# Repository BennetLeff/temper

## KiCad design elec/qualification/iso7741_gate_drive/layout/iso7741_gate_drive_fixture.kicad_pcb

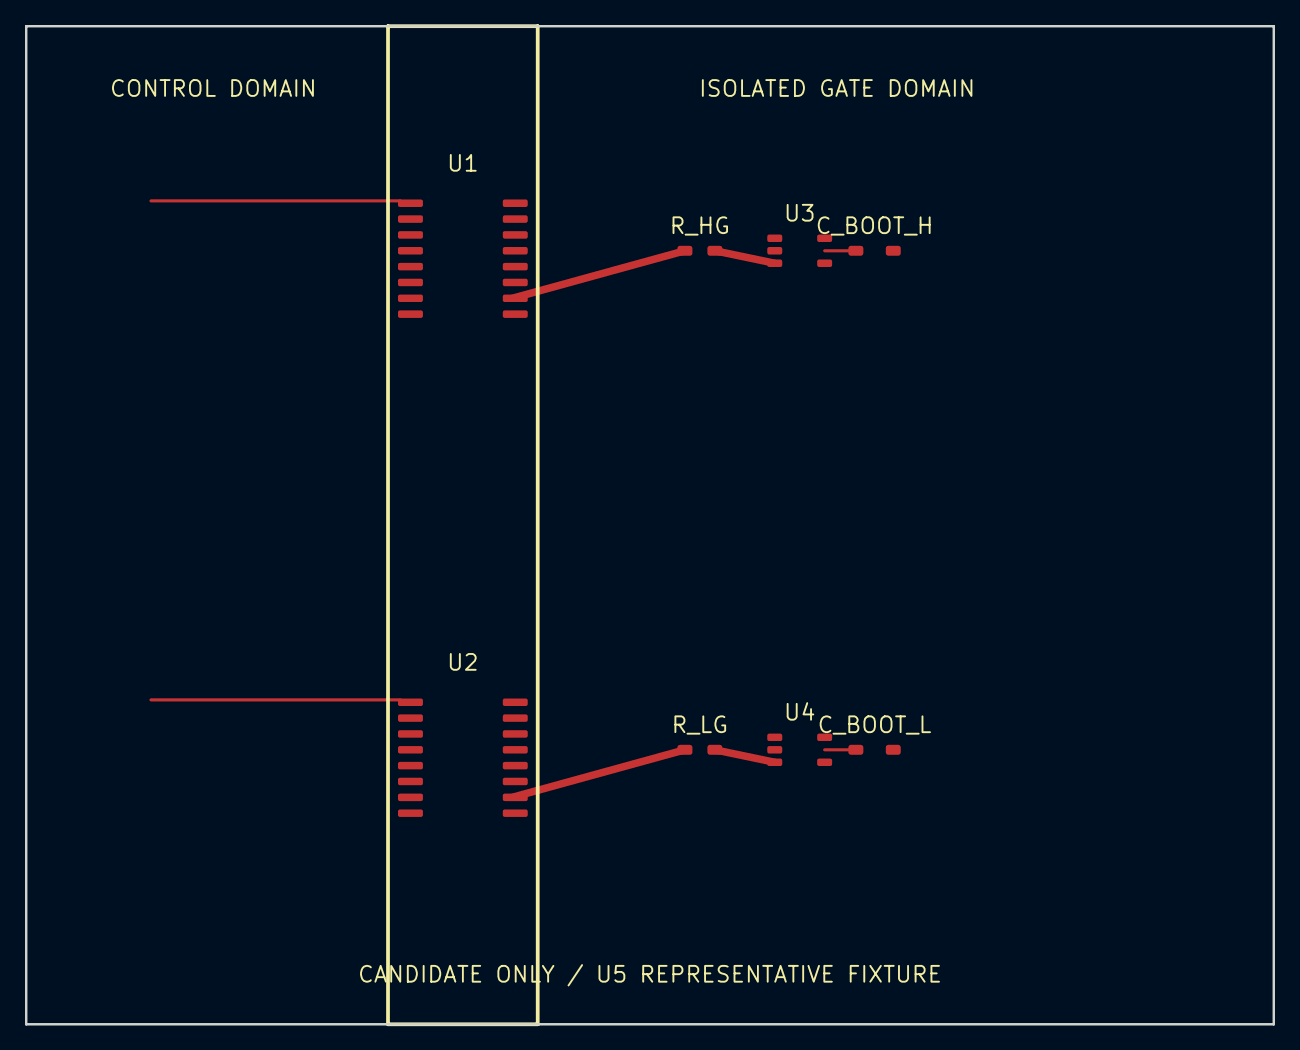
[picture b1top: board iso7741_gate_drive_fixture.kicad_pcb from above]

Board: 2 copper layers, 100.0 x 80.0 mm, 8 parts (0 on the bottom side), 12 nets.

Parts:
C_BOOT_H: 100nF; Bootstrap_HS
C_BOOT_L: 100nF; Bootstrap_LS
R_HG: 4R7_GATE; R_0603_1608Metric
R_LG: 4R7_GATE; R_0603_1608Metric
U1, U2: ISO7741FQDWWRQ1; ISO7741_DWW16
U3, U4: UCC27517AQDBVRQ1; Package_DBV5

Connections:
+15V_HS: C_BOOT_H.2, U3.5
+15V_LS: C_BOOT_L.2, U4.5
CTRL_GND: U1.3 (GND1), U1.5 (GND1), U1.7 (GND1), U2.3 (GND1), U2.5 (GND1), U2.7 (GND1)
GATE_HS: R_HG.1, R_HG.2, U1.10 (Y1), U1.11 (Y2), U3.3
GATE_HS_RETURN: U1.9 (GND2), U1.12 (GND2), U3.2
GATE_LS: R_LG.1, R_LG.2, U2.10 (Y1), U2.11 (Y2), U4.3
GATE_LS_RETURN: U2.9 (GND2), U2.12 (GND2), U4.2
GATE_SAFE_HS: U1.6 (EN1), U3.4
GATE_SAFE_LS: U2.6 (EN1), U4.4
ISO_HS_VDD: U1.4 (VCC1), U1.8 (VCC1)
ISO_LS_OUT: U1.15 (Y3), U3.1, U4.1
ISO_LS_VDD: U1.13 (VCC2), U1.14 (VCC2), U1.16 (VCC2), U2.4 (VCC1), U2.8 (VCC1), U2.13 (VCC2), U2.14 (VCC2), U2.16 (VCC2)

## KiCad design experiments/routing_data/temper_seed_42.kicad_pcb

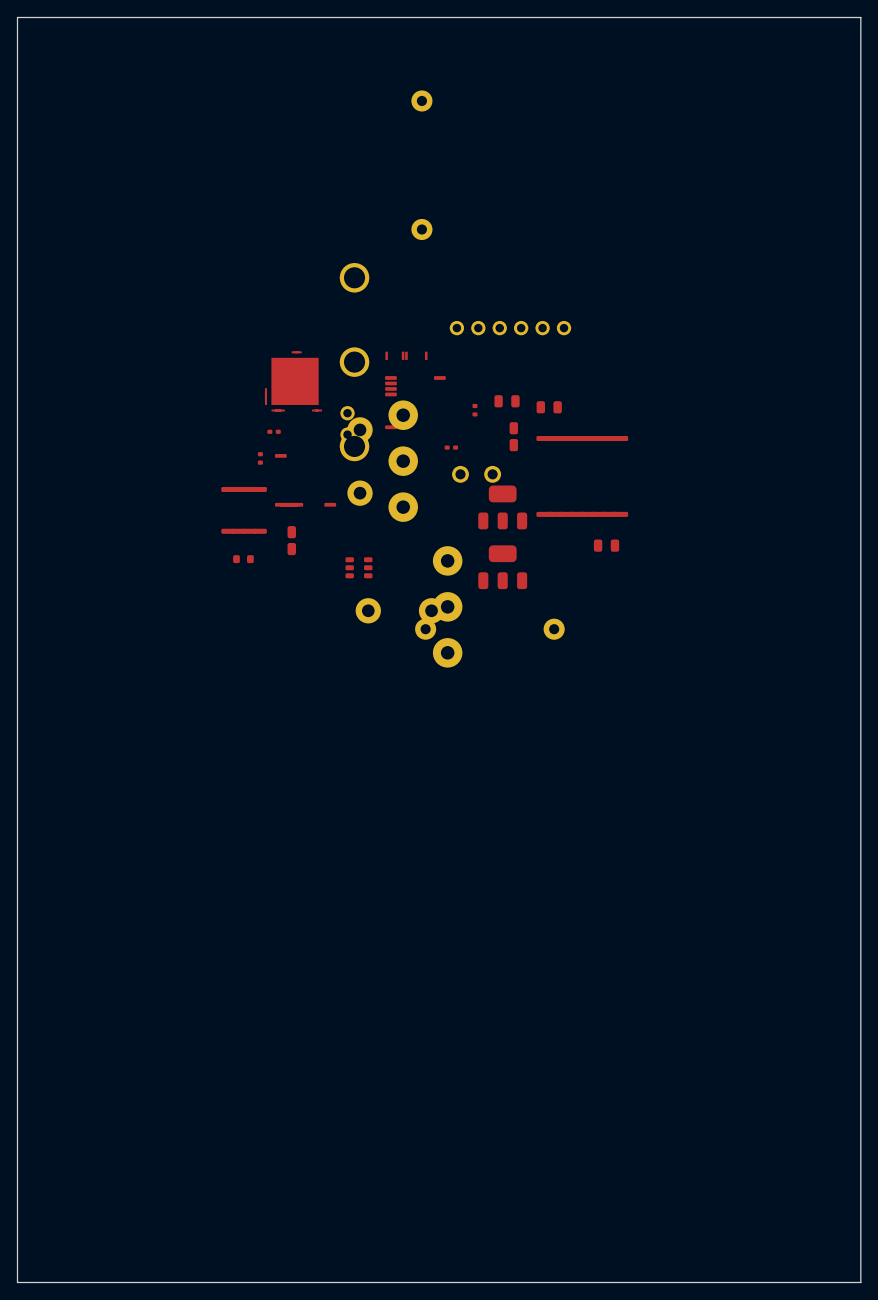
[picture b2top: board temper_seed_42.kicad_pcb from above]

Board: 4 copper layers, 100.0 x 150.0 mm, 33 parts (0 on the bottom side), 23 nets, no tracks yet.

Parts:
C_BOOT: 10uF; C_0805_2012Metric
C_BUS1, C_BUS2: 330uF/400V; CP_Radial_D18.0mm_P7.50mm
C_CT_FILT: 100pF; C_0603_1608Metric
C_MCU_1, C_MCU_2, C_MCU_3: 100nF; C_0402_1005Metric
C_MCU_4: 10uF; C_0402_1005Metric
C_VCC: 10uF; C_0805_2012Metric
D1, D2: 1N5408; D_DO-201AD_P15.24mm_Horizontal
J_AC_IN: IEC_C14; IEC_C14_Male
J_COIL: Coil; PhoenixContact_MCV_1,5_2-G-3.81_1x02_P3.81mm_Vertical
J_DEBUG: Debug; PinHeader_1x06_P2.54mm_Vertical
J_NTC: NTC; PinHeader_1x02_P2.54mm_Vertical
J_USB: USB_C; USB_C_Receptacle_HRO_TYPE-C-31-M-12
MAX31865: MAX31865; TSSOP-20_4.4x6.5mm_P0.65mm
MH1, MH2, MH3, MH4: MountingHole_3.2mm_M3
Q1, Q2: IKW40N120H3; TO-247-3_Horizontal_TabDown
R_BURDEN: 33R; R_0805_2012Metric
R_GATE_H: 4.7R; R_0805_2012Metric
R_GATE_L: 4.7R; R_0805_2012Metric
U_BUCK: LMR51430; SOT-23-6
U_CT: MAX31865; TSSOP-20_4.4x6.5mm_P0.65mm
U_GATE: UCC21550; SOIC-16W_7.5x10.3mm_P1.27mm
U_LDO_3V3: AMS1117-3.3; SOT-223-3_TabPin2
U_LDO_5V: AMS1117-5.0; SOT-223-3_TabPin2
U_MCU: ESP32-S3-WROOM-1; QFN-56-1EP_7x7mm_P0.4mm_EP5.6x5.6mm
U_OPAMP_CT: LM358; SOIC-8_3.9x4.9mm_P1.27mm

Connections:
+3V3: C_MCU_1.1, C_MCU_2.1, C_MCU_3.1, C_MCU_4.1, J_DEBUG.2, MAX31865.20, U_CT.20, U_LDO_3V3.2, U_LDO_3V3.4, U_MCU.1
+5V: U_BUCK.2, U_BUCK.4, U_LDO_3V3.3, U_LDO_5V.2, U_LDO_5V.4, U_OPAMP_CT.7, U_OPAMP_CT.8
+15V: C_VCC.1, U_BUCK.3, U_GATE.1, U_GATE.11, U_LDO_5V.3
AC_L: D1.1, J_AC_IN.1
AC_N: D2.2, J_AC_IN.2
CGND: C_VCC.2, U_GATE.5, U_GATE.6, U_GATE.7, U_GATE.8
DC_BUS+: C_BUS1.1, C_BUS2.1, D1.2, Q1.3
GATE_H: Q1.1, R_GATE_H.1, R_GATE_H.2, U_GATE.15
GATE_L: Q2.1, R_GATE_L.1, R_GATE_L.2, U_GATE.10
GND: C_CT_FILT.2, C_MCU_1.2, C_MCU_2.2, C_MCU_3.2, C_MCU_4.2, J_AC_IN.3, J_COIL.2, J_DEBUG.1, J_NTC.2, J_USB.A1, J_USB.A12, MAX31865.10, R_BURDEN.2, U_BUCK.1, U_BUCK.5, U_BUCK.6, U_CT.10, U_LDO_3V3.1, U_LDO_5V.1, U_MCU.2, U_MCU.57, U_OPAMP_CT.4
I_SENSE: C_CT_FILT.1, R_BURDEN.1, U_MCU.15, U_OPAMP_CT.1, U_OPAMP_CT.2, U_OPAMP_CT.3, U_OPAMP_CT.5, U_OPAMP_CT.6
PGND: C_BUS1.2, C_BUS2.2, Q2.2, U_GATE.12, U_GATE.13
PWM_H: U_GATE.2, U_MCU.13
PWM_L: U_GATE.3, U_MCU.14
SPI_CLK: MAX31865.1, U_CT.1, U_MCU.20
SPI_CS_TEMP: U_CT.4, U_MCU.23
SPI_MISO: MAX31865.3, U_CT.3, U_MCU.22
SPI_MOSI: MAX31865.2, U_CT.2, U_MCU.21
SW_NODE: C_BOOT.2, J_COIL.1, Q1.2, Q2.3, U_GATE.9, U_GATE.16
TEMP_SENSE: J_NTC.1, MAX31865.4
USB_D+: J_USB.A6, U_MCU.40
USB_D-: J_USB.B6, U_MCU.41
VCC_BOOT: C_BOOT.1, U_GATE.14
